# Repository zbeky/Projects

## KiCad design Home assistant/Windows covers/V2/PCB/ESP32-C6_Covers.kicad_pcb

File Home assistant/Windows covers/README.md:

# Automatic window blinds

Body can be printed from PLA, PETG, ABS, etc.

## Additional parts:<br>
1 piece ESP32-WROOM-32D - https://www.aliexpress.com/item/32959541446.html<br>
2 pieces hall sensor rotary sensor - https://www.aliexpress.com/item/4000170678550.html<br>
2 pieces mini XLR 5 pin connector - https://www.aliexpress.com/item/4000105190839.html<br>
2 pieces 4mm-6mm coupler - https://www.aliexpress.com/item/4000194793728.html<br>
2 pieces 3mm-4mm coupler - https://www.aliexpress.com/item/4000194793728.html<br>

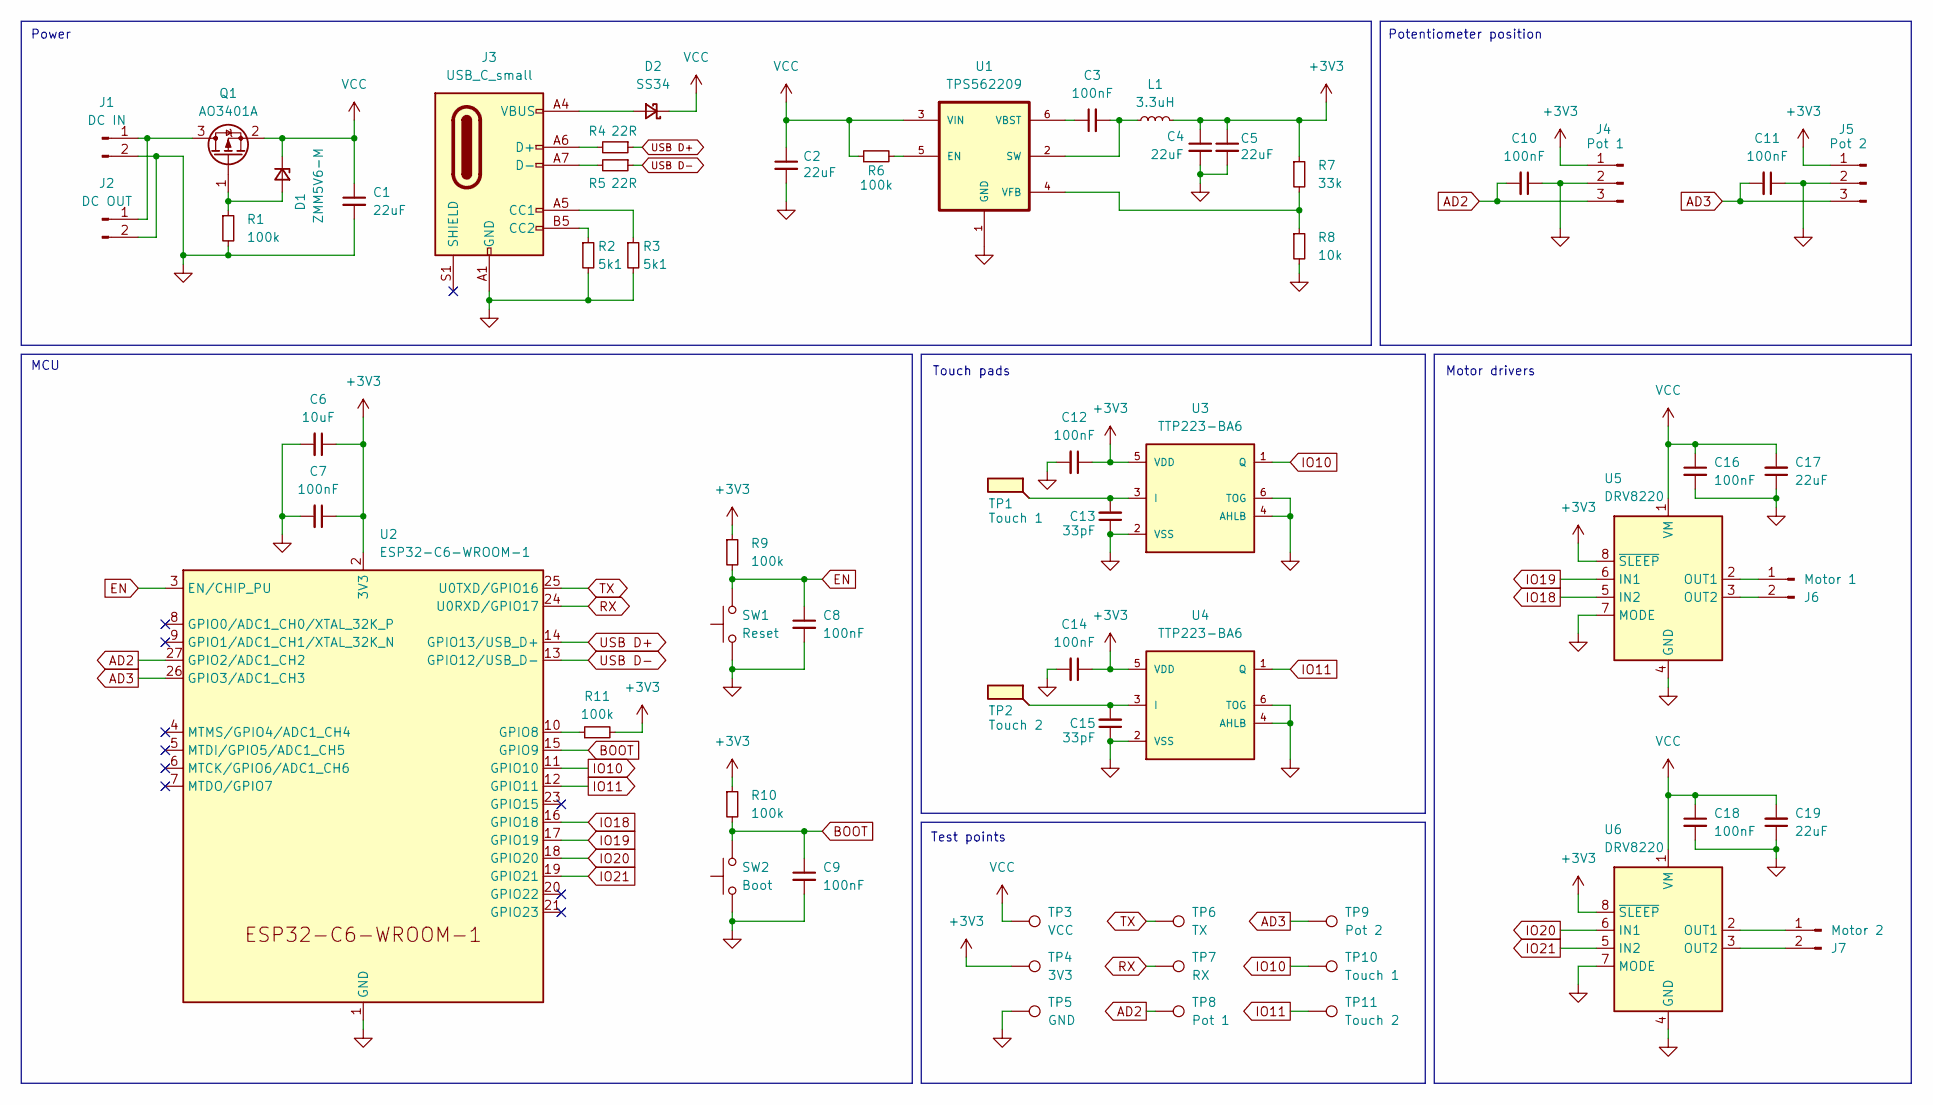
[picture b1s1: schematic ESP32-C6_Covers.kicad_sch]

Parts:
C1, C2, C4, C5, C17, C19: 22uF; C_0805_2012Metric
C3, C7, C8, C9, C10, C11, C12, C14, C16, C18: 100nF; C_0402_1005Metric
C6: 10uF; C_0805_2012Metric
C13, C15: 33pF; C_0402_1005Metric
D1: ZMM5V6-M; D_MiniMELF
D2: SS34; D_SMA
J1: DC IN; JST_XH_B2B-XH-A_1x02_P2.50mm_Vertical
J2: DC OUT; JST_XH_B2B-XH-A_1x02_P2.50mm_Vertical
J3: USB_C_small; USB_C_Receptacle_GCT_USB4105-xx-A_16P_TopMnt_Horizontal
J4: Pot 1; JST_XH_B3B-XH-A_1x03_P2.50mm_Vertical
J5: Pot 2; JST_XH_B3B-XH-A_1x03_P2.50mm_Vertical
J6: Motor 1; JST_XH_B2B-XH-A_1x02_P2.50mm_Vertical
J7: Motor 2; JST_XH_B2B-XH-A_1x02_P2.50mm_Vertical
L1: 3.3uH; L_1008_2520Metric
Q1: AO3401A; SOT-23
R1, R6, R9, R10, R11: 100k; R_0402_1005Metric
R2, R3: 5k1; R_0603_1608Metric
R4, R5: 22R; R_0603_1608Metric
R7: 33k; R_0402_1005Metric
R8: 10k; R_0402_1005Metric
SW1: Reset; SW_Push_1P1T_XKB_TS-1187A
SW2: Boot; SW_Push_1P1T_XKB_TS-1187A
TP1: Touch 1; Touch_pad_arrow
TP2: Touch 2; Touch_pad_arrow
TP3: VCC; TestPoint_Pad_D1.0mm
TP4: 3V3; TestPoint_Pad_D1.0mm
TP5: GND; TestPoint_Pad_D1.0mm
TP6: TX; TestPoint_Pad_D1.0mm
TP7: RX; TestPoint_Pad_D1.0mm
TP8: Pot 1; TestPoint_Pad_D1.0mm
TP9: Pot 2; TestPoint_Pad_D1.0mm
TP10: Touch 1; TestPoint_Pad_D1.0mm
TP11: Touch 2; TestPoint_Pad_D1.0mm
U1: TPS562209; TI_TPS562209
U2: ESP32-C6-WROOM-1
U3, U4: TTP223-BA6; SOT23-6
U5, U6: DRV8220; WSON-8-1EP_2x2mm_P0.5mm_EP0.9x1.6mm

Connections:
+3V3: C4.1, C5.1, C6.1, C7.1, C12.1, C14.1, J4.1, J5.1, L1.2, R7.1, R9.1, R10.1, R11.2, TP4.1, U2.2 (3V3), U3.5 (VDD), U4.5 (VDD), U5.8 (~SLEEP), U6.8 (~SLEEP)
AD2: C10.2, J4.3, TP8.1, U2.27 (GPIO2/ADC1_CH2)
AD3: C11.2, J5.3, TP9.1, U2.26 (GPIO3/ADC1_CH3)
BOOT: C9.1, R10.2, SW2.2, U2.15 (GPIO9)
EN: C8.1, R9.2, SW1.2, U2.3 (EN/CHIP_PU)
GND: C1.2, C2.2, C4.2, C5.2, C6.2, C7.2, C8.2, C9.2, C10.1, C11.1, C12.2, C13.1, C14.2, C15.1, C16.2, C17.1, C18.2, C19.1, J1.2, J2.2, J3.A1 (GND), J3.A12 (GND), J3.B1 (GND), J3.B12 (GND), J4.2, J5.2, R1.2, R2.2, R3.2, R8.2, SW1.1, SW2.1, TP5.1, U1.1 (GND), U2.1 (GND), U2.28 (GND), U2.29 (GND), U3.2 (VSS), U3.4 (AHLB), U3.6 (TOG), U4.2 (VSS), U4.4 (AHLB), U4.6 (TOG), U5.4 (GND), U5.7 (MODE), U5.9 (GND), U6.4 (GND), U6.7 (MODE), U6.9 (GND)
IO10: TP10.1, U2.11 (GPIO10), U3.1 (Q)
IO11: TP11.1, U2.12 (GPIO11), U4.1 (Q)
IO18: U2.16 (GPIO18), U5.5 (IN2)
IO19: U2.17 (GPIO19), U5.6 (IN1)
IO20: U2.18 (GPIO20), U6.6 (IN1)
IO21: U2.19 (GPIO21), U6.5 (IN2)
unnamed: D1.2 (A), Q1.1 (G), R1.1
unnamed: D2.2 (A), J3.A4 (VBUS), J3.A9 (VBUS), J3.B4 (VBUS), J3.B9 (VBUS)
unnamed: J1.1, J2.1, Q1.3 (D)
unnamed: J3.A5 (CC1), R3.1
unnamed: J3.B5 (CC2), R2.1
unnamed: J3.A6 (D+), J3.B6 (D+), R4.2
unnamed: J3.A7 (D-), J3.B7 (D-), R5.2
unnamed: J6.1, U5.2 (OUT1)
unnamed: J6.2, U5.3 (OUT2)
unnamed: J7.1, U6.2 (OUT1)
unnamed: J7.2, U6.3 (OUT2)
unnamed: R6.2, U1.5 (EN)
unnamed: C3.2, L1.1, U1.2 (SW)
unnamed: C3.1, U1.6 (VBST)
unnamed: R7.2, R8.1, U1.4 (VFB)
unnamed: R11.1, U2.10 (GPIO8)
unnamed: C13.2, TP1.1, U3.3 (I)
unnamed: C15.2, TP2.1, U4.3 (I)
RX: TP7.1, U2.24 (U0RXD/GPIO17)
TX: TP6.1, U2.25 (U0TXD/GPIO16)
USB D+: R4.1, U2.14 (GPIO13/USB_D+)
USB D-: R5.1, U2.13 (GPIO12/USB_D-)
VCC: C1.1, C2.1, C16.1, C17.2, C18.1, C19.2, D1.1 (K), D2.1 (K), Q1.2 (S), R6.1, TP3.1, U1.3 (VIN), U5.1 (VM), U6.1 (VM)

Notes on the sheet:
MCU
Touch pads
Power
Test points
Motor drivers
Potentiometer position

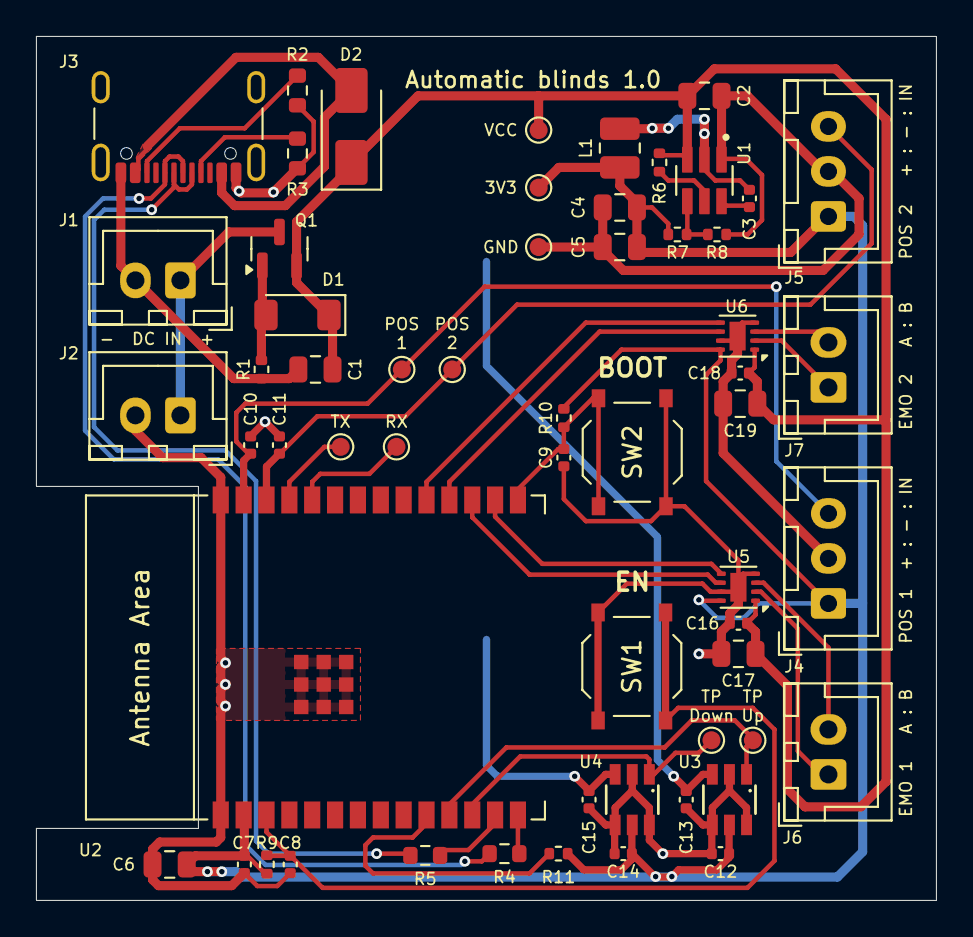
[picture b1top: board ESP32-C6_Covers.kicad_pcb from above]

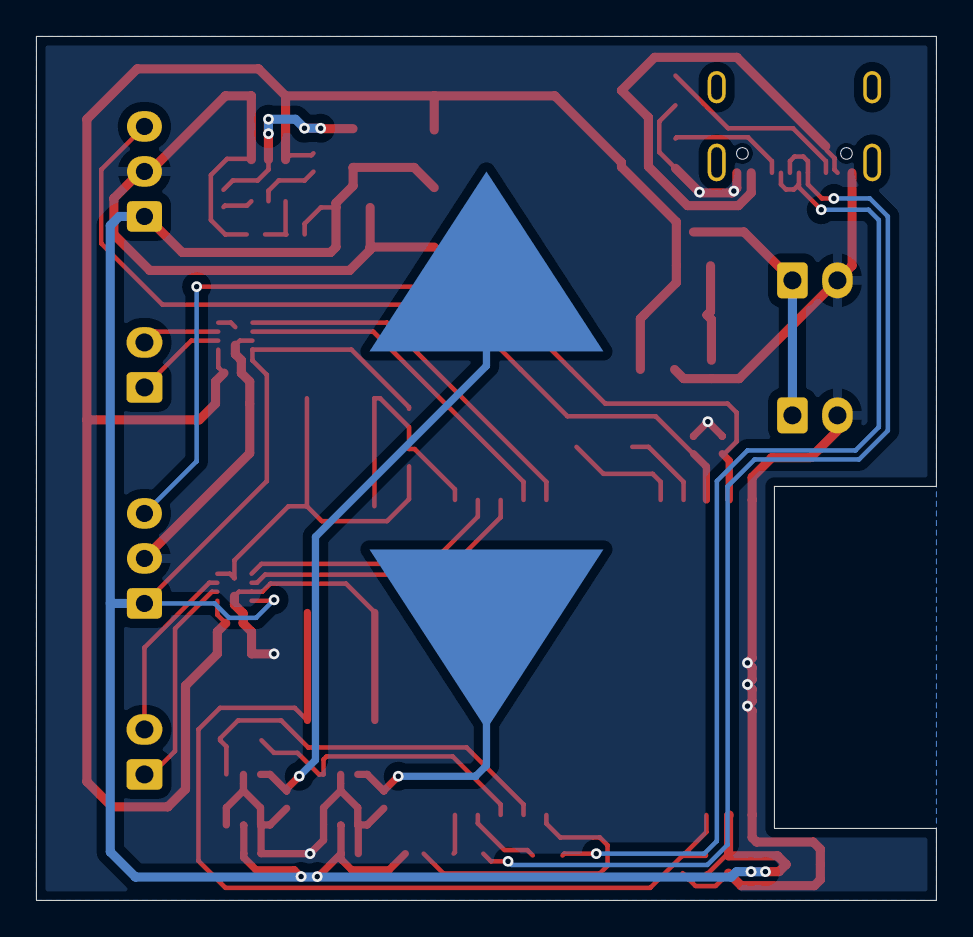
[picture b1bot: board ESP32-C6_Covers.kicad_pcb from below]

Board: 2 copper layers, 50.0 x 48.0 mm, 60 parts (2 on the bottom side), 35 nets.

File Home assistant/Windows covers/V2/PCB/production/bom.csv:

Designator,Footprint,Quantity,Value,LCSC Part #
"C1, C17, C19, C2, C4, C5",0805,6,22uF,
"C10, C11, C12, C14, C16, C18, C3, C7, C8, C9",0402,10,100nF,
"C13, C15",0402,2,33pF,
C6,0805,1,10uF,
D1,D_MiniMELF,1,ZMM5V6-M,
D2,D_SMA,1,SS34,
J3,USB_C_Receptacle_GCT_USB4105-xx-A_16P_TopMnt_Horizontal,1,USB_C_small,
L1,1008,1,3.3uH,
Q1,SOT-23,1,AO3401A,
"R1, R10, R11, R6, R9",0402,5,100k,
"R2, R3",0603,2,5k1,
"R4, R5",0603,2,22R,
R7,0402,1,33k,
R8,0402,1,10k,
SW1,SW_Push_1P1T_XKB_TS-1187A,1,Reset,
SW2,SW_Push_1P1T_XKB_TS-1187A,1,Boot,
TP1,Touch_pad_arrow,1,Touch 1,
TP10,TestPoint_Pad_D1.0mm,1,Touch 1,
TP11,TestPoint_Pad_D1.0mm,1,Touch 2,
TP2,Touch_pad_arrow,1,Touch 2,
TP3,TestPoint_Pad_D1.0mm,1,VCC,
TP4,TestPoint_Pad_D1.0mm,1,3V3,
TP5,TestPoint_Pad_D1.0mm,1,GND,
TP6,TestPoint_Pad_D1.0mm,1,TX,
TP7,TestPoint_Pad_D1.0mm,1,RX,
TP8,TestPoint_Pad_D1.0mm,1,Pot 1,
TP9,TestPoint_Pad_D1.0mm,1,Pot 2,
U1,TI_TPS562209,1,TPS562209,
"U3, U4",SOT23-6,2,TTP223-BA6,
"U5, U6",WSON-8-1EP_2x2mm_P0.5mm_EP0.9x1.6mm,2,DRV8220,

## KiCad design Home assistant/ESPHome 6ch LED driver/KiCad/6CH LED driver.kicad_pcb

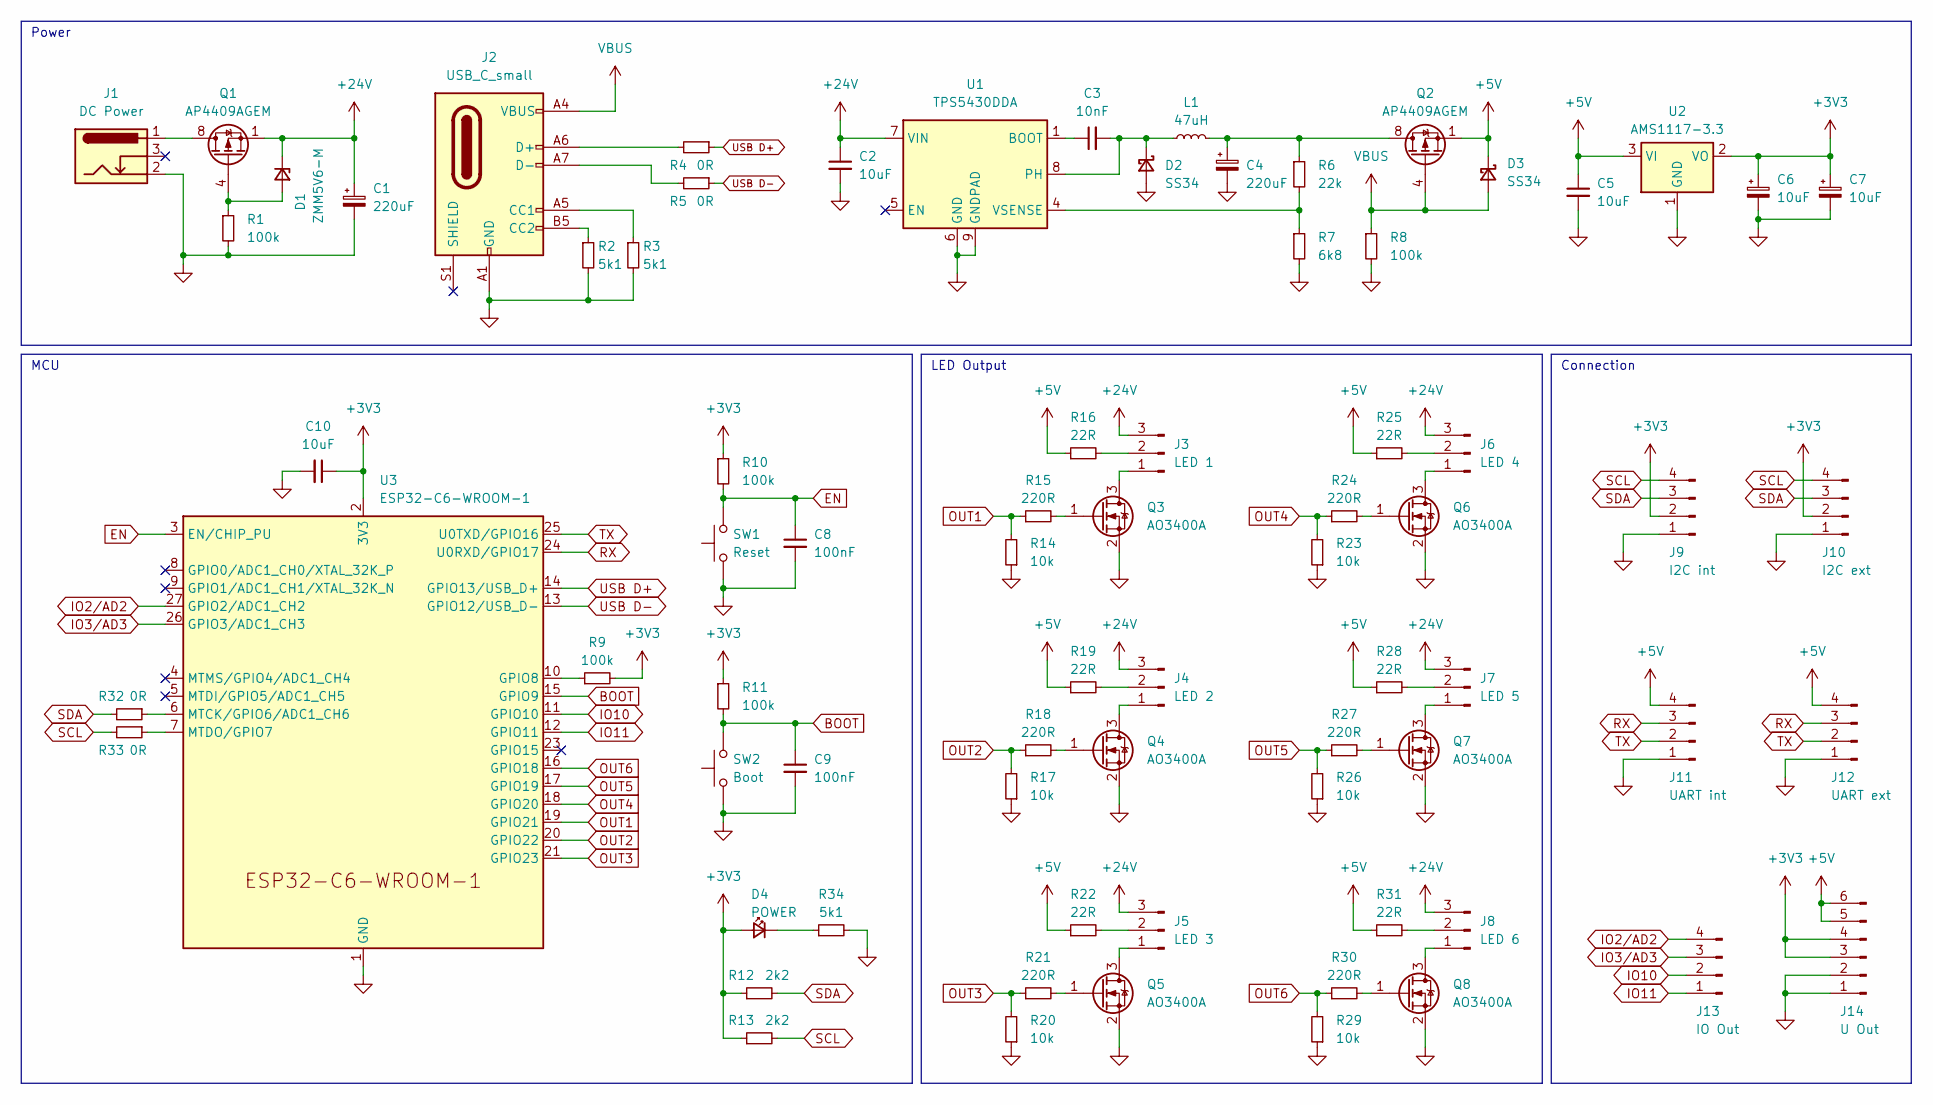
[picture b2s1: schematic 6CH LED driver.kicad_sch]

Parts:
C1, C4: 220uF; CP_Elec_8x11.9
C2, C5, C10: 10uF; C_0805_2012Metric
C3: 10nF; C_0402_1005Metric
C6, C7: 10uF; CP_EIA-3216-12_Kemet-S
C8, C9: 100nF; C_0603_1608Metric
D1: ZMM5V6-M; D_MiniMELF
D2, D3: SS34; D_SMA
D4: POWER; LED_0603_1608Metric
J1: DC Power; BarrelJack_Wuerth_694106106102_2.0x5.5mm
J2: USB_C_small; USB_C_Receptacle_GCT_USB4105-xx-A_16P_TopMnt_Horizontal
J3: LED 1; JST_XH_S3B-XH
J4: LED 2; JST_XH_S3B-XH
J5: LED 3; JST_XH_S3B-XH
J6: LED 4; JST_XH_S3B-XH
J7: LED 5; JST_XH_S3B-XH
J8: LED 6; JST_XH_S3B-XH
J9: I2C int; PinHeader_1x04_P2.54mm_Vertical
J10: I2C ext; JST_XH_S4B-XH
J11: UART int; PinHeader_1x04_P2.54mm_Vertical
J12: UART ext; JST_XH_S4B-XH
J13: IO Out; PinHeader_1x04_P2.54mm_Vertical
J14: U Out; PinHeader_1x06_P2.54mm_Vertical
L1: 47uH; L_Bourns_SRP7028A_7.3x6.6mm
Q1, Q2: AP4409AGEM; SOIC-8_3.9x4.9mm_P1.27mm
Q3, Q4, Q5, Q6, Q7, Q8: AO3400A; SOT-23
R1, R8, R9, R10, R11: 100k; R_0603_1608Metric
R2, R3, R34: 5k1; R_0603_1608Metric
R4, R5: 0R; R_0603_1608Metric
R6: 22k; R_0603_1608Metric
R7: 6k8; R_0603_1608Metric
R12, R13: 2k2; R_0603_1608Metric
R14, R17, R20, R23, R26, R29: 10k; R_0603_1608Metric
R15, R18, R21, R24, R27, R30: 220R; R_0603_1608Metric
R16, R19, R22, R25, R28, R31: 22R; R_1206_3216Metric
R32, R33: 0R; R_1206_3216Metric
SW1: Reset; SW_Push_1P1T_XKB_TS-1187A
SW2: Boot; SW_Push_1P1T_XKB_TS-1187A
U1: TPS5430DDA; TI_SO-PowerPAD-8
U2: AMS1117-3.3; SOT-223-3_TabPin2
U3: ESP32-C6-WROOM-1

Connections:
+3V3: C6.1, C7.1, C10.1, D4.2 (A), J9.2, J10.2, J14.3, J14.4, R9.2, R10.1, R11.1, R12.1, R13.1, U2.2 (VO), U3.2 (3V3)
+5V: C5.1, D3.1 (K), J11.4, J12.4, J14.5, J14.6, Q2.1 (S), Q2.2 (S), Q2.3 (S), R16.1, R19.1, R22.1, R25.1, R28.1, R31.1, U2.3 (VI)
+24V: C1.1, C2.1, D1.1 (K), J3.3, J4.3, J5.3, J6.3, J7.3, J8.3, Q1.1 (S), Q1.2 (S), Q1.3 (S), U1.7 (VIN)
BOOT: C9.1, R11.2, SW2.2, U3.15 (GPIO9)
EN: C8.1, R10.2, SW1.2, U3.3 (EN/CHIP_PU)
GND: C1.2, C2.2, C4.2, C5.2, C6.2, C7.2, C8.2, C9.2, C10.2, D2.2 (A), J1.2, J2.A1 (GND), J2.A12 (GND), J2.B1 (GND), J2.B12 (GND), J9.1, J10.1, J11.1, J12.1, J14.1, J14.2, Q3.2 (S), Q4.2 (S), Q5.2 (S), Q6.2 (S), Q7.2 (S), Q8.2 (S), R1.2, R2.2, R3.2, R7.2, R8.2, R14.1, R17.1, R20.1, R23.1, R26.1, R29.1, R34.2, SW1.1, SW2.1, U1.6 (GND), U1.9 (GNDPAD), U2.1 (GND), U3.1 (GND), U3.28 (GND), U3.29 (GND)
IO2/AD2: J13.4, U3.27 (GPIO2/ADC1_CH2)
IO3/AD3: J13.3, U3.26 (GPIO3/ADC1_CH3)
IO10: J13.2, U3.11 (GPIO10)
IO11: J13.1, U3.12 (GPIO11)
unnamed: C4.1, L1.2, Q2.5 (D), Q2.6 (D), Q2.7 (D), Q2.8 (D), R6.1
unnamed: D1.2 (A), Q1.4 (G), R1.1
unnamed: C3.2, D2.1 (K), L1.1, U1.8 (PH)
unnamed: D4.1 (K), R34.1
unnamed: J1.1, Q1.5 (D), Q1.6 (D), Q1.7 (D), Q1.8 (D)
unnamed: J2.A5 (CC1), R3.1
unnamed: J2.B5 (CC2), R2.1
unnamed: J2.A6 (D+), J2.B6 (D+), R4.2
unnamed: J2.A7 (D-), J2.B7 (D-), R5.2
unnamed: J3.1, Q3.3 (D)
unnamed: J3.2, R16.2
unnamed: J4.1, Q4.3 (D)
unnamed: J4.2, R19.2
unnamed: J5.1, Q5.3 (D)
unnamed: J5.2, R22.2
unnamed: J6.1, Q6.3 (D)
unnamed: J6.2, R25.2
unnamed: J7.1, Q7.3 (D)
unnamed: J7.2, R28.2
unnamed: J8.1, Q8.3 (D)
unnamed: J8.2, R31.2
unnamed: Q3.1 (G), R15.2
unnamed: Q4.1 (G), R18.2
unnamed: Q5.1 (G), R21.2
unnamed: Q6.1 (G), R24.2
unnamed: Q7.1 (G), R27.2
unnamed: Q8.1 (G), R30.2
unnamed: C3.1, U1.1 (BOOT)
unnamed: R6.2, R7.1, U1.4 (VSENSE)
unnamed: R9.1, U3.10 (GPIO8)
unnamed: R32.1, U3.6 (MTCK/GPIO6/ADC1_CH6)
unnamed: R33.1, U3.7 (MTDO/GPIO7)
OUT1: R14.2, R15.1, U3.19 (GPIO21)
OUT2: R17.2, R18.1, U3.20 (GPIO22)
OUT3: R20.2, R21.1, U3.21 (GPIO23)
OUT4: R23.2, R24.1, U3.18 (GPIO20)
OUT5: R26.2, R27.1, U3.17 (GPIO19)
OUT6: R29.2, R30.1, U3.16 (GPIO18)
RX: J11.3, J12.3, U3.24 (U0RXD/GPIO17)
SCL: J9.4, J10.4, R13.2, R33.2
SDA: J9.3, J10.3, R12.2, R32.2
TX: J11.2, J12.2, U3.25 (U0TXD/GPIO16)
USB D+: R4.1, U3.14 (GPIO13/USB_D+)
USB D-: R5.1, U3.13 (GPIO12/USB_D-)
VBUS: D3.2 (A), J2.A4 (VBUS), J2.A9 (VBUS), J2.B4 (VBUS), J2.B9 (VBUS), Q2.4 (G), R8.1

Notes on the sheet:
MCU
LED Output
Connection
Power

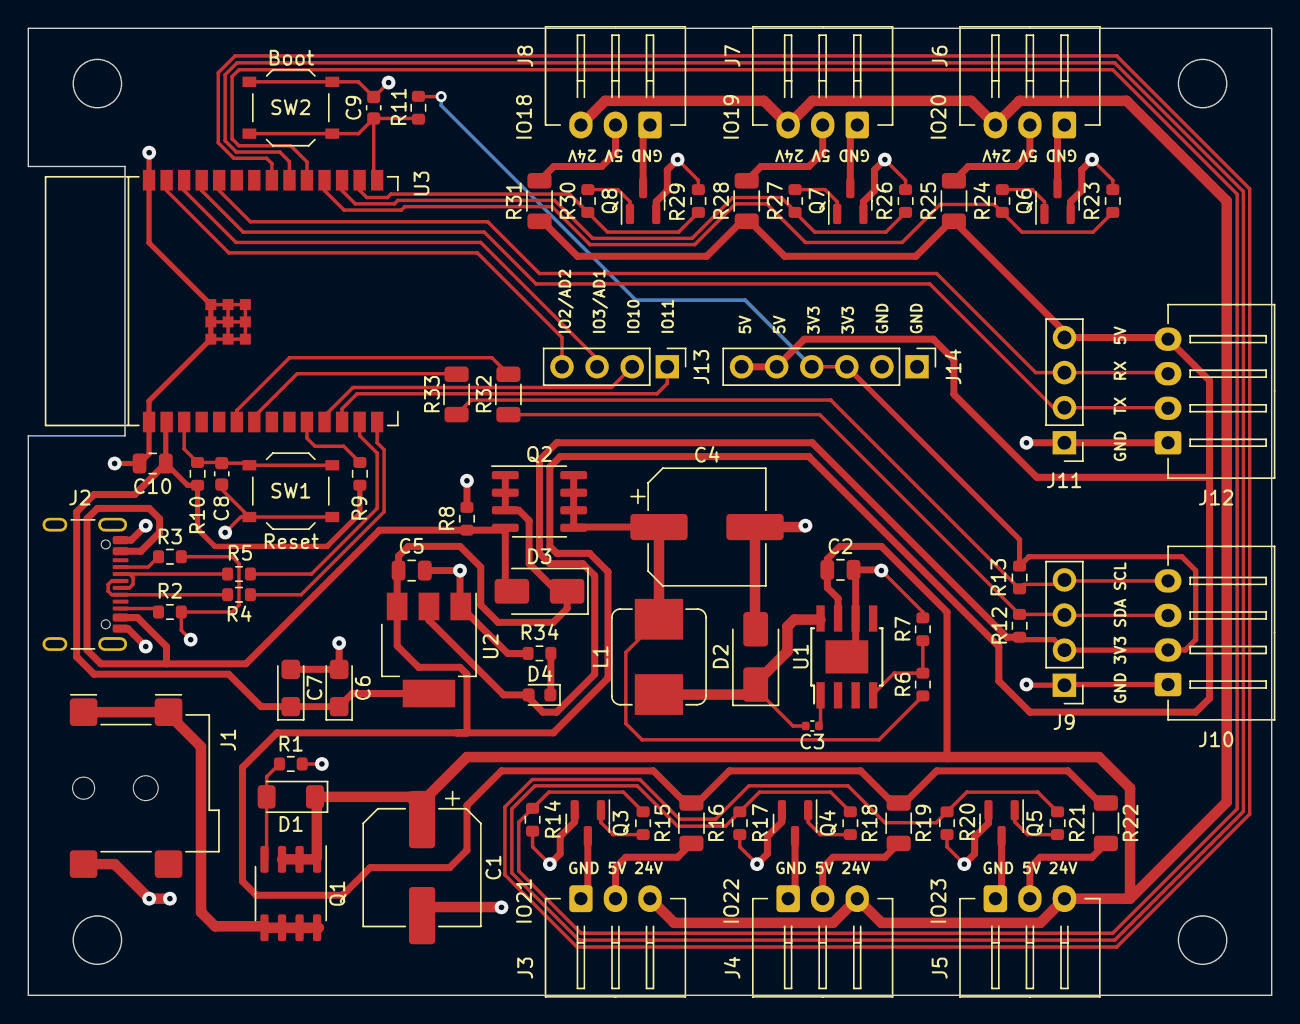
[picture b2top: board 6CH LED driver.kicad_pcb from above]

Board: 2 copper layers, 90.0 x 70.0 mm, 76 parts (0 on the bottom side), 55 nets.

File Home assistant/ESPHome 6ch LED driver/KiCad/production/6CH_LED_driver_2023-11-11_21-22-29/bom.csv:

Designator,Footprint,Quantity,Value,LCSC Part #
"C1, C4",CP_Elec_8x11.9,2,220uF,
"C10, C2, C5",0805,3,10uF,
C3,0402,1,10nF,
"C6, C7",CP_EIA-3216-12_Kemet-S,2,10uF,
"C8, C9",0603,2,100nF,
D1,D_MiniMELF,1,ZMM5V6-M,
"D2, D3",D_SMA,2,SS34,
D4,0603,1,POWER,
J1,BarrelJack_Wuerth_694106106102_2.0x5.5mm,1,DC Power,
J2,USB_C_Receptacle_GCT_USB4105-xx-A_16P_TopMnt_Horizontal,1,USB_C_small,
L1,L_Bourns_SRP7028A_7.3x6.6mm,1,47uH,
"Q1, Q2",SOIC-8_3.9x4.9mm_P1.27mm,2,AP4409AGEM,
"Q3, Q4, Q5, Q6, Q7, Q8",SOT-23,6,AO3400A,
"R1, R10, R8, R9",0603,4,100k,
"R11, R2, R3",0603,3,5k1,
"R12, R13",0603,2,2k2,
"R14, R17, R20, R23, R26, R29",0603,6,10k,
"R15, R18, R21, R24, R27, R30",0603,6,220R,
"R16, R19, R22, R25, R28, R31",1206,6,22R,
"R32, R33",1206,2,0R,
"R4, R5",0603,2,0R,
R6,0603,1,22k,
R7,0603,1,6k8,
SW1,SW_Push_1P1T_XKB_TS-1187A,1,Reset,
SW2,SW_Push_1P1T_XKB_TS-1187A,1,Boot,
U1,TI_SO-PowerPAD-8,1,TPS5430DDA,
U2,SOT-223-3_TabPin2,1,AMS1117-3.3,

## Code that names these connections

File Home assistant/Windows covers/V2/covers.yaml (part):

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    entity_category: "diagnostic"
    icon: mdi:wifi
  - platform: adc
    pin: GPIO2
    id: pos_bot
    update_interval: 1ms
    attenuation: 0db
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            return {};
          }
  - platform: adc
    pin: GPIO3
    id: pos_top
    update_interval: 1ms
    attenuation: 0db
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
output:      
  - platform: ledc
    pin: GPIO20
    id: motor_top_a
    frequency: 19531Hz
  - platform: ledc
    pin: GPIO21
    id: motor_top_b
    frequency: 19531Hz
  - platform: ledc
    pin: GPIO18
    id: motor_bot_a
    frequency: 19531Hz
  - platform: ledc
    pin: GPIO19
    id: motor_bot_b
    frequency: 19531Hz
    
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
binary_sensor:
  - platform: gpio
    pin: GPIO10
    id: btn_open
    filters: 
      - delayed_on_off: 50ms
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                              id: cover_bot
                              position: 99% # 100% calls cover.open
  - platform: gpio
    pin: GPIO11
    id: btn_close
    filters: 
      - delayed_on_off: 50ms
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
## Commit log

2020-11-09 Xmas tree update
2020-11-09 Include libraries
2020-11-09 Fingerprint opener
2020-11-09 Fingerprint
2020-11-12 Add 3D printed case
2020-11-12 Enable FET on startup
2020-11-13 Updated PCB
2020-11-15 Add ESPHome 4way light switch
2020-11-15 New gerber
2020-11-25 Add Lenovo M10 docking station
2020-11-26 Fingerprint update
2020-12-01 Don't block fingeprint by lost connection
2020-12-01 Capital letters
2020-12-04 Fix capacitor value
2020-12-07 Add schematic for fingerprint
2020-12-11 Triac christmass tree
2020-12-14 4way switch update
2021-01-14 Fingerprint sensor reset function
2021-03-19 C5 Running indicators and ATTiny85 PWM shift
2021-03-23 Add new projects
2021-03-25 Add operating states to cover
2021-05-21 Filter noise
2021-11-09 Add Peugeot 3008 High beams dimming
2023-10-23 Add ESPHome 4ch CCT LED driver
2023-12-10 Add 6ch esphome led driver
2023-12-12 Fix USB
2024-03-25 Fix boot mode
2024-04-14 Add windows blinds V2 PCB
2024-08-13 Add V2 covers
2025-12-06 Cleanup
